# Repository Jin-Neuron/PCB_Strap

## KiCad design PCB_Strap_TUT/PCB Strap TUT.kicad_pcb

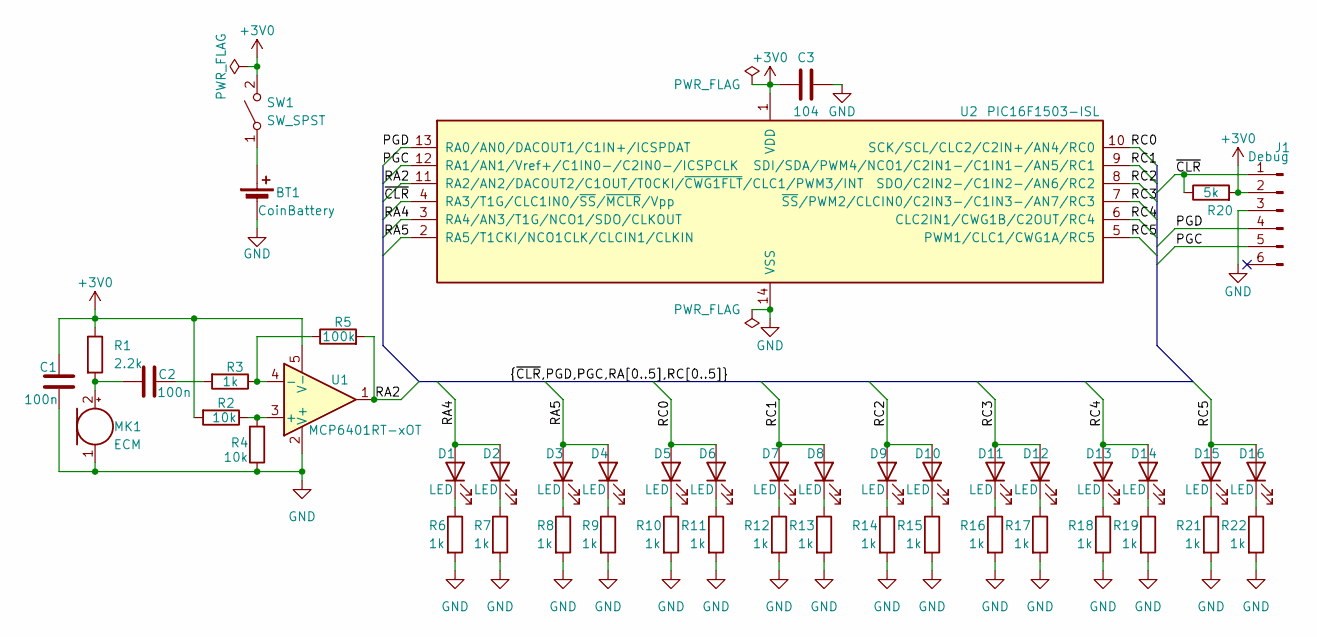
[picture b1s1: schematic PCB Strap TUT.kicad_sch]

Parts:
BT1: CoinBattery; BatteryHolder_Multicomp_BC-2001_1x2032
C1, C2: 100n; C_0402_1005Metric
C3: 104; C_0402_1005Metric
D1, D2, D3, D4, D5, D6, D7, D8, D9, D10, D11, D12, D13, D14, D15, D16: LED; LED_0603_1608Metric
J1: Debug; PinHeader_1x06_P2.54mm_Vertical
MK1: ECM; POM-2244P-C3310-2-R
R1: 2.2k; R_0603_1608Metric
R2, R4: 10k; R_0603_1608Metric
R3, R6, R7, R8, R9, R10, R11, R12, R13, R14, R15, R16, R17, R18, R19, R21, R22: 1k; R_0603_1608Metric
R5: 100k; R_0603_1608Metric
R20: 5k; R_0603_1608Metric
SW1: SW_SPST; SW_Slide-03_Wuerth-WS-SLTV_10x2.5x6.4_P2.54mm
U1: MCP6401RT-xOT; SOT-23-5
U2: PIC16F1503-ISL; SOIC-14_3.9x8.7mm_P1.27mm

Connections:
+3V0: C1.2, C3.1, J1.2, R1.1, R2.2, R20.2, SW1.2 (B), U1.5 (V-), U2.1 (VDD)
/PGC: J1.5, U2.12 (RA1/AN1/Vref+/C1IN0-/C2IN0-/ICSPCLK)
/PGD: J1.4, U2.13 (RA0/AN0/DACOUT1/C1IN+/ICSPDAT)
/RA2: R5.2, U1.1, U2.11 (RA2/AN2/DACOUT2/C1OUT/T0CKI/~CWG1FLT/CL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)
/RA4: D1.2 (A), D2.2 (A), U2.3 (RA4/AN3/T1G/NCO1/SDO/CLKOUT)
/RA5: D3.2 (A), D4.2 (A), U2.2 (RA5/T1CKI/NCO1CLK/CLCIN1/CLKIN)
/RC0: D5.2 (A), D6.2 (A), U2.10 (SCK/SCL/CLC2/C2IN+/AN4/RC0)
/RC1: D7.2 (A), D8.2 (A), U2.9 (SDI/SDA/PWM4/NCO1/C2IN1-/C1IN1-/AN5/RC1)
/RC2: D9.2 (A), D10.2 (A), U2.8 (SDO/C2IN2-/C1IN2-/AN6/RC2)
/RC3: D11.2 (A), D12.2 (A), U2.7 (~SS/PWM2/CLCIN0/C2IN3-/C1IN3-/AN7/RC3)
/RC4: D13.2 (A), D14.2 (A), U2.6 (CLC2IN1/CWG1B/C2OUT/RC4)
/RC5: D15.2 (A), D16.2 (A), U2.5 (PWM1/CLC1/CWG1A/RC5)
/~CLR: J1.1, R20.1, U2.4 (RA3/T1G/CLC1IN0/~SS/~MCLR/Vpp)
GND: BT1.2 (-), C1.1, C3.2, J1.3, MK1.1 (-), R4.1, R6.2, R7.2, R8.2, R9.2, R10.2, R11.2, R12.2, R13.2, R14.2, R15.2, R16.2, R17.2, R18.2, R19.2, R21.2, R22.2, U1.2 (V+), U2.14 (VSS)
unnamed: BT1.1 (+), SW1.1 (A)
unnamed: C2.2, R3.2
unnamed: D1.1 (K), R6.1
unnamed: D2.1 (K), R7.1
unnamed: D3.1 (K), R8.1
unnamed: D4.1 (K), R9.1
unnamed: D5.1 (K), R10.1
unnamed: D6.1 (K), R11.1
unnamed: D7.1 (K), R12.1
unnamed: D8.1 (K), R13.1
unnamed: D9.1 (K), R14.1
unnamed: D10.1 (K), R15.1
unnamed: D11.1 (K), R16.1
unnamed: D12.1 (K), R17.1
unnamed: D13.1 (K), R18.1
unnamed: D14.1 (K), R19.1
unnamed: D15.1 (K), R21.1
unnamed: D16.1 (K), R22.1
unnamed: C2.1, MK1.2 (+), R1.2
unnamed: R2.1, R4.2, U1.3 (+)
unnamed: R3.1, R5.1, U1.4 (-)

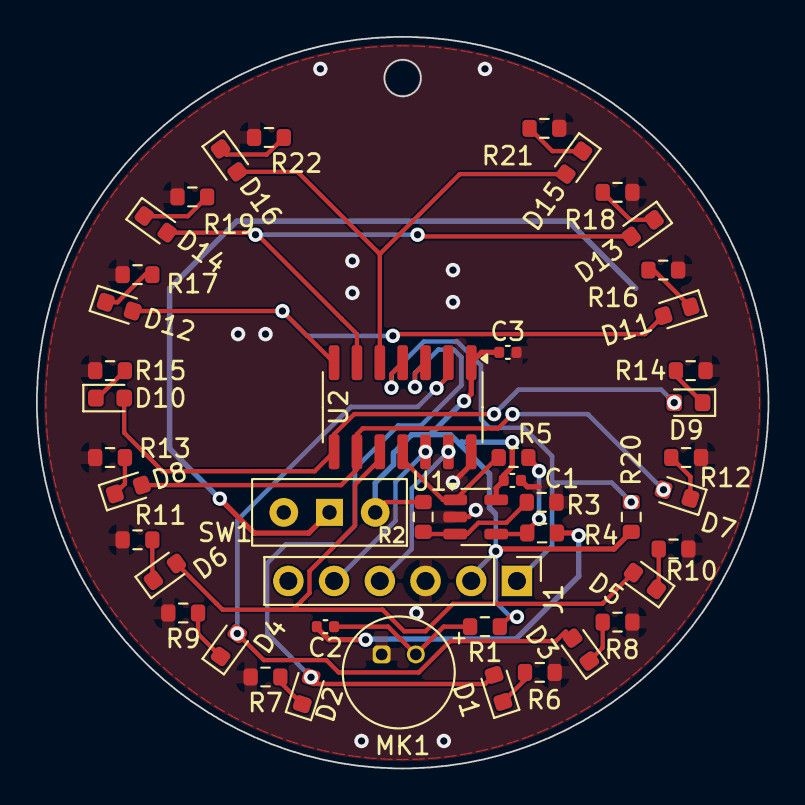
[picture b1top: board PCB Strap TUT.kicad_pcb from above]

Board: 2 copper layers, 40.6 x 40.6 mm, 47 parts (1 on the bottom side), 35 nets.

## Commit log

2025-08-09 remove some files
2025-08-09 adjust some silk and add EasyEDA Files
2025-08-09 add some pictures
2025-09-30 add test PIC ASM to PCB_Strap_TUT
2025-10-01 test ADC and add Amp
2026-01-10 'UpdateProgram'
2026-01-15 'editProgram'
2026-01-15 'ignoreSetting'
